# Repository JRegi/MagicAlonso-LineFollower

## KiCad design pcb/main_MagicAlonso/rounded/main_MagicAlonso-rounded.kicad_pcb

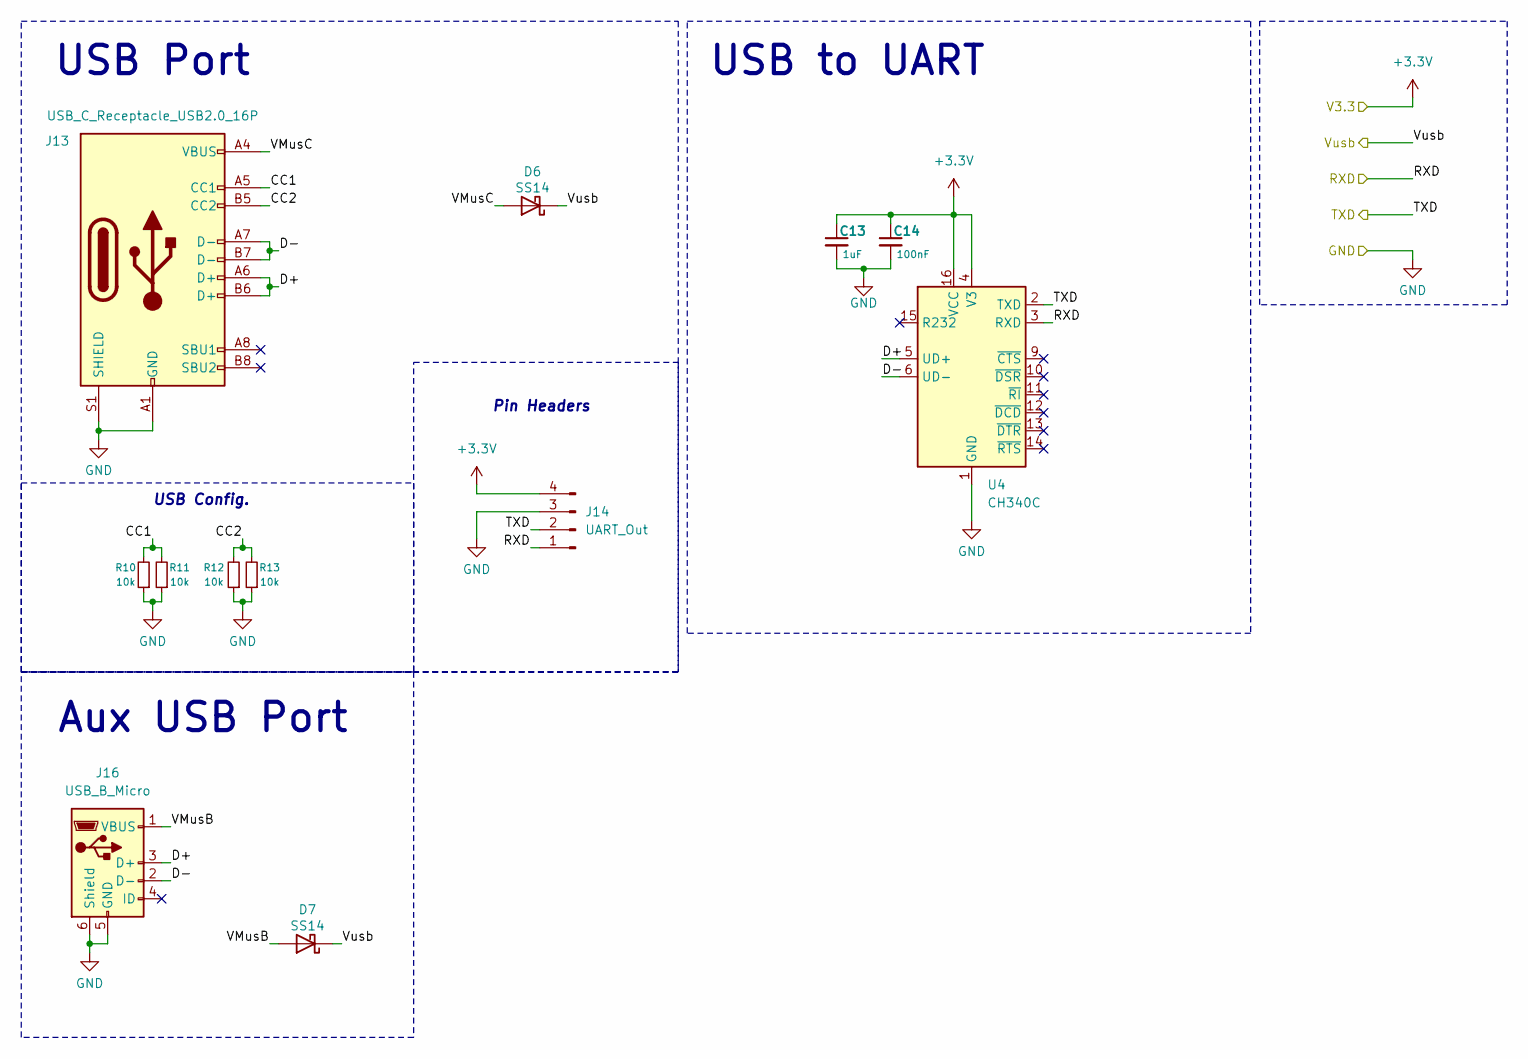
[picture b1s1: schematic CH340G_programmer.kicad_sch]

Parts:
C13: 1uF; C_0805_2012Metric
C14: 100nF; C_0603_1608Metric
D6, D7: SS14; D_SMA
J13: USB_C_Receptacle_USB2.0_16P; USB_C_Receptacle_GCT_USB4110
J14: UART_Out; JST_XH_S4B-XH-A_1x04_P2.50mm_Horizontal
J16: USB_B_Micro; USB_Micro-B_Amphenol_10104110_Horizontal
R10, R11, R12, R13: 10k; R_0603_1608Metric
U4: CH340C; SOIC-16_3.9x9.9mm_P1.27mm

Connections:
+3.3V: C13.1, C14.1, J14.4, U4.4 (V3), U4.16 (VCC); also elsewhere on the board
/CH340C/CC1: J13.A5 (CC1), R10.2, R11.2
/CH340C/CC2: J13.B5 (CC2), R12.2, R13.2
/CH340C/D+: J13.A6 (D+), J13.B6 (D+), J16.3 (D+), U4.5 (UD+)
/CH340C/D-: J13.A7 (D-), J13.B7 (D-), J16.2 (D-), U4.6 (UD-)
/CH340C/VMusB: D7.2 (A), J16.1 (VBUS)
/CH340C/VMusC: D6.2 (A), J13.A4 (VBUS), J13.A9 (VBUS), J13.B4 (VBUS), J13.B9 (VBUS)
/RX: J14.1, U4.3 (RXD); also elsewhere on the board
/TX: J14.2, U4.2 (TXD); also elsewhere on the board
/Vb: D6.1 (K), D7.1 (K); also elsewhere on the board
GND: C13.2, C14.2, J13.A1 (GND), J13.A12 (GND), J13.B1 (GND), J13.B12 (GND), J13.S1 (SHIELD), J14.3, J16.5 (GND), J16.6 (Shield), R10.1, R11.1, R12.1, R13.1, U4.1 (GND); also elsewhere on the board

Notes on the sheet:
USB to UART
Pin Headers
USB Config.
USB Port
Aux USB Port

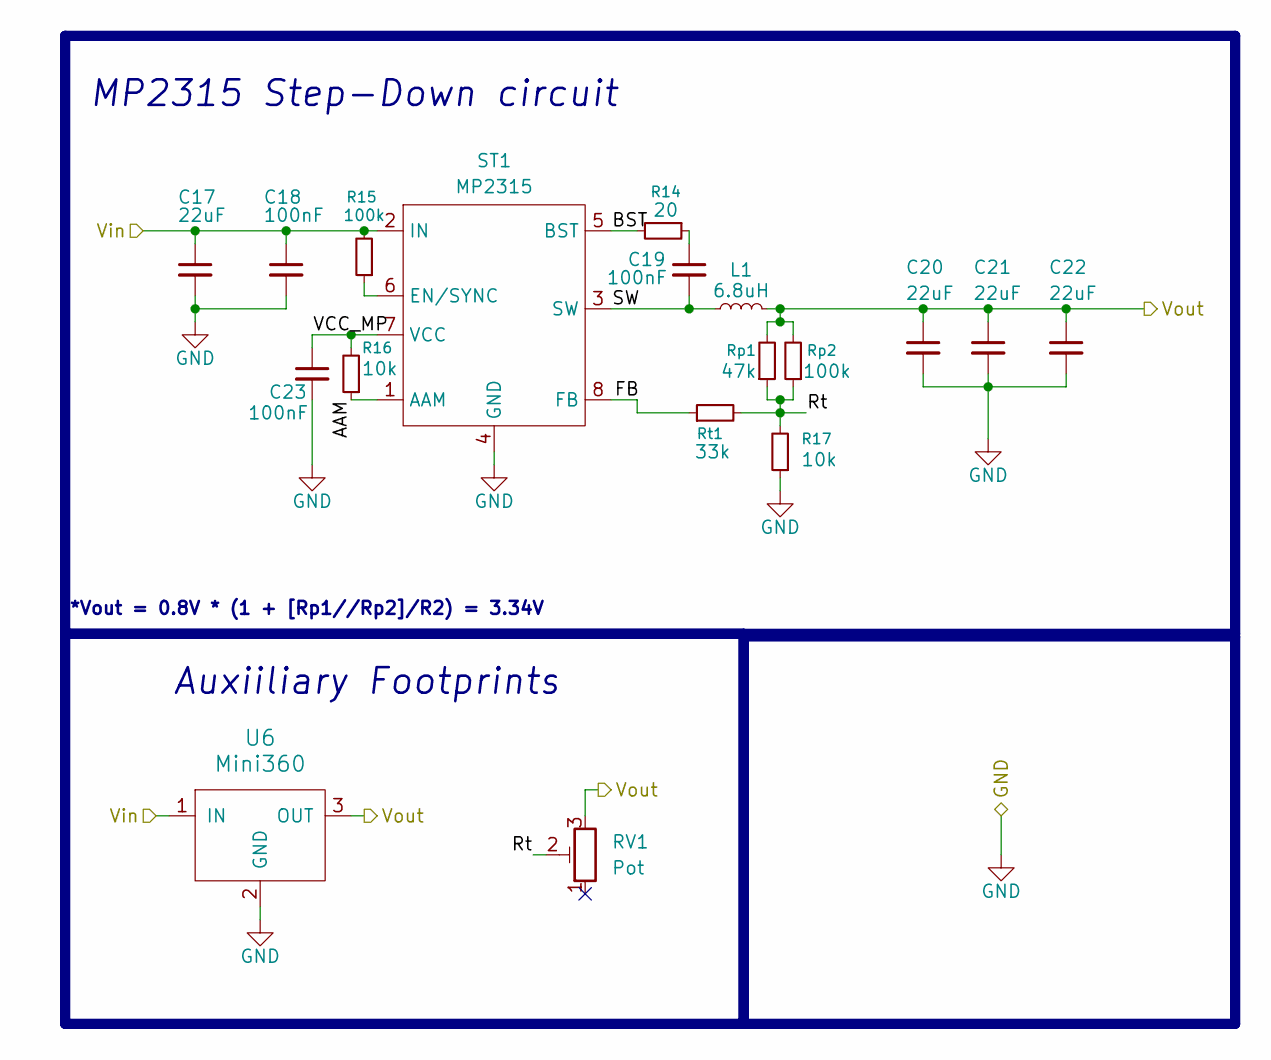
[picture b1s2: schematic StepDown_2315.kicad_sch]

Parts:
C17, C20, C21, C22: 22uF; C_0805_2012Metric
C18, C19, C23: 100nF; C_0603_1608Metric
L1: 6.8uH; L_TDK_SLF6025
R14: 20; R_0805_2012Metric
R15: 100k; R_0603_1608Metric
R16: 10k; R_0603_1608Metric
R17: 10k; R_0805_2012Metric
RV1: Pot; Potentiometer_Vishay_TS53YJ_Vertical
Rp1: 47k; R_0805_2012Metric
Rp2: 100k; R_0805_2012Metric
Rt1: 33k; R_0603_1608Metric
ST1: MP2315; TSOT-23-8
U6: Mini360; Mini360_step-down

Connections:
+3.3V: C20.1, C21.1, C22.1, L1.2, RV1.3, Rp1.2, Rp2.2, U6.3 (OUT); also elsewhere on the board
/StepDown_2315/AAM: R16.1, ST1.1 (AAM)
/StepDown_2315/BST: R14.2, ST1.5 (BST)
/StepDown_2315/FB: Rt1.1, ST1.8 (FB)
/StepDown_2315/Rt: R17.2, RV1.2, Rp1.1, Rp2.1, Rt1.2
/StepDown_2315/SW: C19.2, L1.1, ST1.3 (SW)
/StepDown_2315/VCC_SW: C23.1, R16.2, ST1.7 (VCC)
/Vb: C17.1, C18.1, R15.2, ST1.2 (IN), U6.1 (IN); also elsewhere on the board
GND: C17.2, C18.2, C20.2, C21.2, C22.2, C23.2, R17.1, ST1.4 (GND), U6.2 (GND); also elsewhere on the board
unnamed: C19.1, R14.1
unnamed: R15.1, ST1.6 (EN/SYNC)

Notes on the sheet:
*Vout = 0.8V * (1 + [Rp1//Rp2]/R2) = 3.34V
Auxiiliary Footprints
MP2315 Step-Down circuit

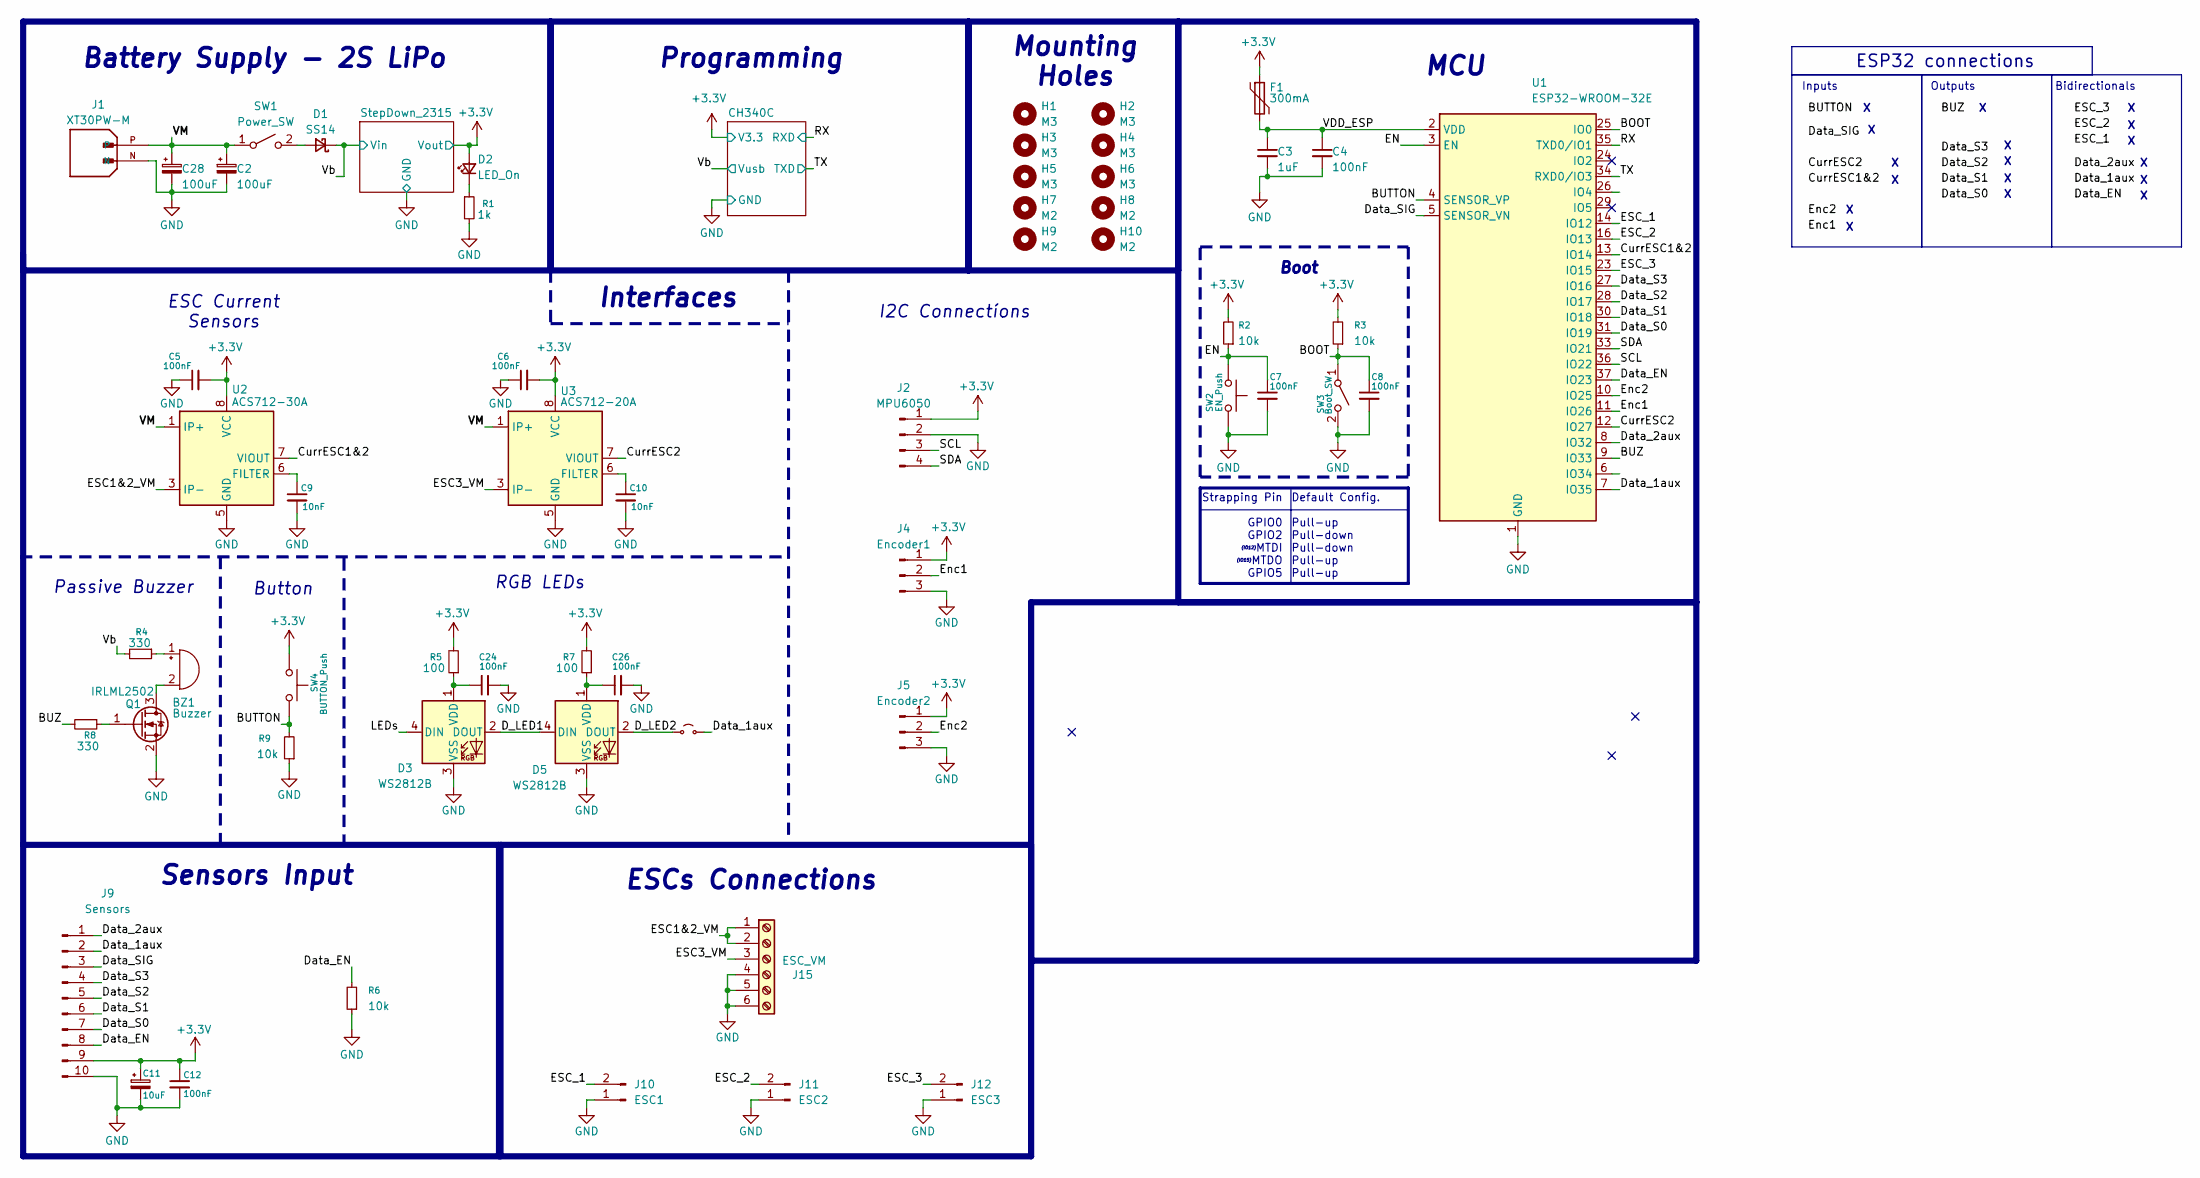
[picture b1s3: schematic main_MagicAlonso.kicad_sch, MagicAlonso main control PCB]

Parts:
BZ1: Buzzer; Buzzer_12x9.5RM7.6
C2, C28: 100uF; CP_Elec_6.3x5.4
C3: 1uF; C_0805_2012Metric
C4, C7, C12, C24, C26: 100nF; C_0805_2012Metric
C5, C6, C8: 100nF; C_0603_1608Metric
C9, C10: 10nF; C_0805_2012Metric
C11: 10uF; C_0805_2012Metric
D1: SS14; D_SMA
D2: LED_On; LED_0805_2012Metric
D3, D5: WS2812B; LED_WS2812B_PLCC4_5.0x5.0mm_P3.2mm
F1: 300mA; Fuse_1812_4532Metric_Pad1.30x3.40mm_HandSolder
H1, H2, H3, H4, H5, H6: M3; MountingHole_3mm
H7, H8, H9, H10: M2; MountingHole_2.2mm_M2
J1: XT30PW-M; AMASS_XT30PW-M; PARTREV 1.2
J2: MPU6050; MPU6050_Module
J4: Encoder1; JST_XH_B3B-XH-A_1x03_P2.50mm_Vertical
J5: Encoder2; JST_XH_B3B-XH-A_1x03_P2.50mm_Vertical
J9: Sensors; JST_XH_S10B-XH-A_1x10_P2.50mm_Horizontal
J10: ESC1; JST_XH_S2B-XH-A_1x02_P2.50mm_Horizontal
J11: ESC2; JST_XH_S2B-XH-A_1x02_P2.50mm_Horizontal
J12: ESC3; JST_XH_S2B-XH-A_1x02_P2.50mm_Horizontal
J15: ESC_VM; TerminalBlock_Phoenix_PT-1,5-6-3.5-H_1x06_P3.50mm_Horizontal
JP1: Jumper_2_Small_Open; R_1206_3216Metric
Q1: IRLML2502; SOT-23
R1: 1k; R_0603_1608Metric
R2, R3: 10k; R_0603_1608Metric
R4: 330; R_1206_3216Metric
R5, R7: 100; R_0805_2012Metric
R6, R9: 10k; R_0805_2012Metric
R8: 330; R_0805_2012Metric
SW1: Power_SW; SW_Slide-03_P2.54_L9_W4_H7
SW2: EN_Push; SW_SPST_CK_RS282G05A3
SW3: Boot_SW; SW_Slide-03_P2.54_L9_W4_H7
SW4: BUTTON_Push; SW_SPST_CK_RS282G05A3
U1: ESP32-WROOM-32E
U2: ACS712-30A; SOIC-8_3.9x4.9mm_P1.27mm
U3: ACS712-20A; SOIC-8_3.9x4.9mm_P1.27mm

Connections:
+3.3V: C5.2, C6.2, C11.1, C12.1, D2.2 (A), F1.1, J2.1, J4.1, J5.1, J9.9, R2.2, R3.2, R5.2, R7.2, SW4.1, U2.8 (VCC), U3.8 (VCC); also elsewhere on the board
/BOOT: C8.1, R3.1, SW3.1 (A), U1.25 (IO0)
/BUTTON: R9.2, SW4.2, U1.4 (SENSOR_VP)
/BUZ: R8.2, U1.9 (IO33)
/CurrESC1&2: U1.13 (IO14), U2.7 (VIOUT)
/CurrESC2: U1.12 (IO27), U3.7 (VIOUT)
/D_LED: D3.2 (DOUT), D5.4 (DIN)
/Data_1aux: J9.2, JP1.2 (B), U1.7 (IO35)
/Data_2aux: J9.1, U1.8 (IO32)
/Data_EN: J9.8, R6.2, U1.37 (IO23)
/Data_S0: J9.7, U1.31 (IO19)
/Data_S1: J9.6, U1.30 (IO18)
/Data_S2: J9.5, U1.28 (IO17)
/Data_S3: J9.4, U1.27 (IO16)
/Data_SIG: J9.3, U1.5 (SENSOR_VN)
/EN: C7.1, R2.1, SW2.1, U1.3 (EN)
/ESC1&2_VM: J15.1, J15.2, U2.3 (IP-), U2.4 (IP-)
/ESC3_VM: J15.3, U3.3 (IP-), U3.4 (IP-)
/ESC_1: J10.2, U1.14 (IO12)
/ESC_2: J11.2, U1.16 (IO13)
/ESC_3: J12.2, U1.23 (IO15)
/Enc1: J4.2, U1.11 (IO26)
/Enc2: J5.2, U1.10 (IO25)
/LEDs: D3.4 (DIN)
/RX: U1.35 (TXD0/IO1); also elsewhere on the board
/SCL: J2.3, U1.36 (IO22)
/SDA: J2.4, U1.33 (IO21)
/TX: U1.34 (RXD0/IO3); also elsewhere on the board
/VDD_ESP: C3.1, C4.1, F1.2, U1.2 (VDD)
/VM: C2.1, C28.1, J1.P, SW1.1 (A), U2.1 (IP+), U2.2 (IP+), U3.1 (IP+), U3.2 (IP+)
/Vb: D1.1 (K), R4.2; also elsewhere on the board
GND: C2.2, C3.2, C4.2, C5.1, C6.1, C7.2, C8.2, C9.2, C10.2, C11.2, C12.2, C24.2, C26.2, C28.2, D3.3 (VSS), D5.3 (VSS), J1.N, J2.2, J4.3, J5.3, J9.10, J10.1, J11.1, J12.1, J15.4, J15.5, J15.6, Q1.2 (S), R1.2, R6.1, R9.1, SW2.2, SW3.2 (B), U1.1 (GND), U1.15 (GND), U1.38 (GND), U1.39 (GND), U2.5 (GND), U3.5 (GND); also elsewhere on the board
unnamed: BZ1.1 (+), R4.1
unnamed: BZ1.2 (-), Q1.3 (D)
unnamed: D1.2 (A), SW1.2 (B)
unnamed: D2.1 (K), R1.1
unnamed: C24.1, D3.1 (VDD), R5.1
unnamed: C26.1, D5.1 (VDD), R7.1
unnamed: D5.2 (DOUT), JP1.1 (A)
unnamed: Q1.1 (G), R8.1
unnamed: C9.1, U2.6 (FILTER)
unnamed: C10.1, U3.6 (FILTER)

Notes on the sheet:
ESC Current Sensors
Strapping Pin GPIO0 GPIO2 MTDI MTDO GPIO5
Inputs
(IO12)
Passive Buzzer
(IO15)
I2C Connectíons
Mounting Holes
ESP32 connections
Battery Supply - 2S LiPo
Sensors Input
MCU
ESCs Connections
Boot
RGB LEDs
Outputs
Button
Interfaces
Bidirectionals
Default Config. Pull-up Pull-down Pull-down Pull-up Pull-up
Programming

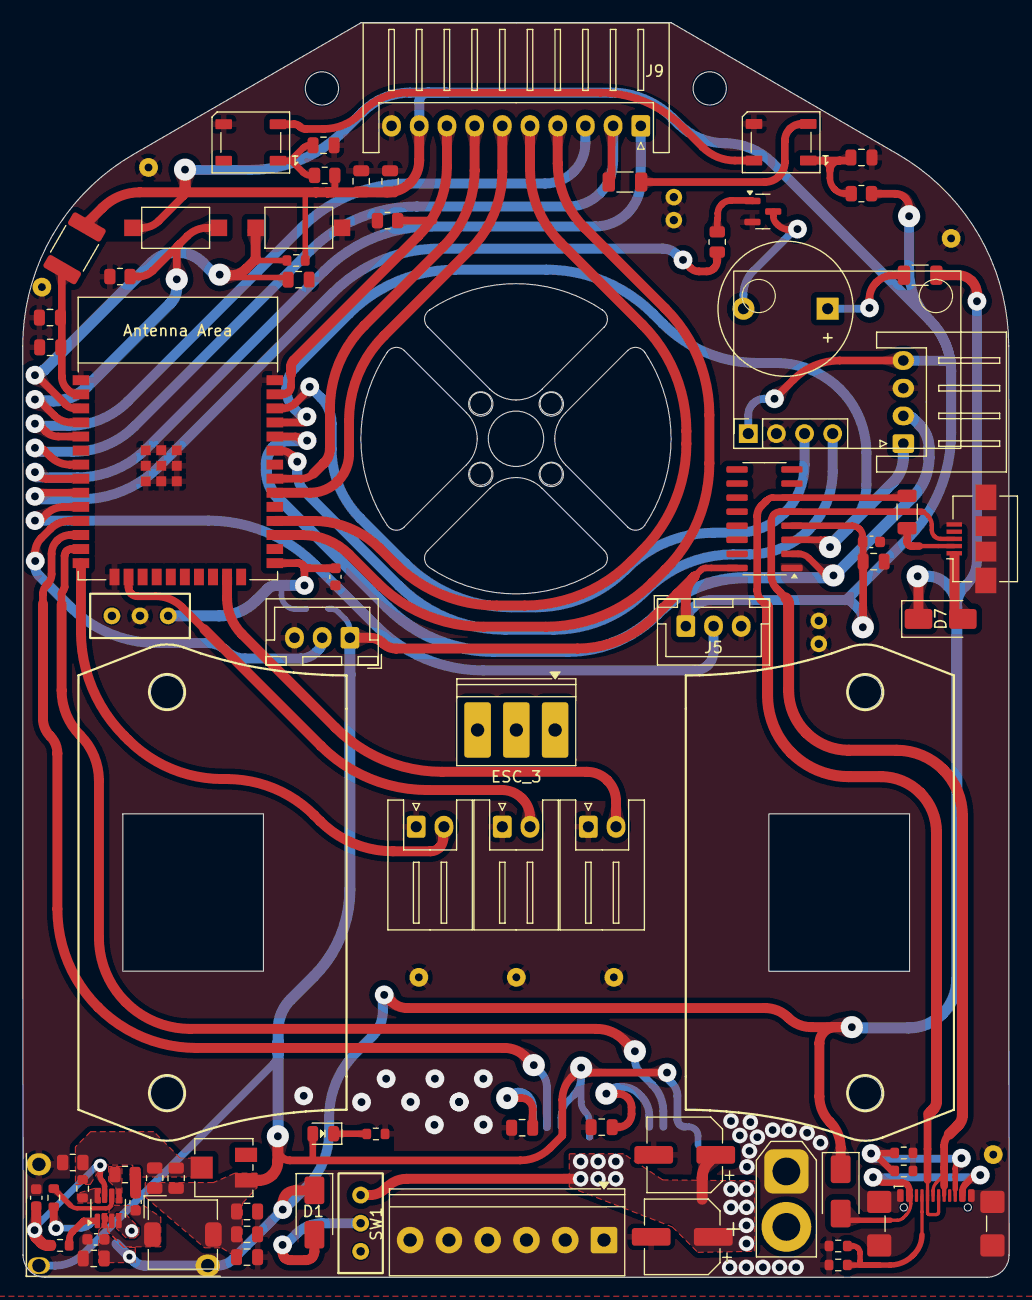
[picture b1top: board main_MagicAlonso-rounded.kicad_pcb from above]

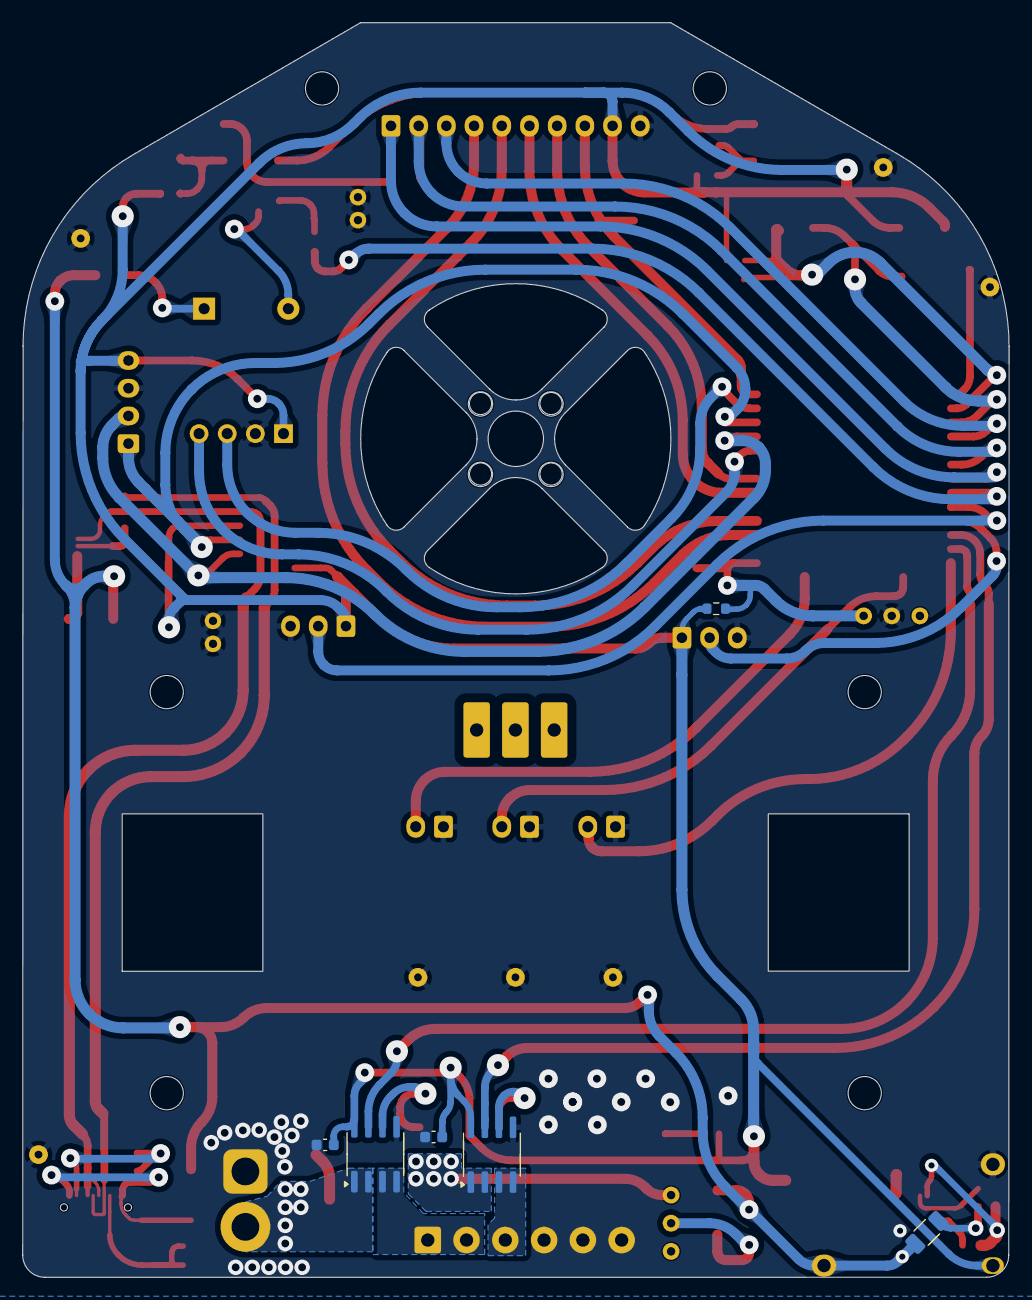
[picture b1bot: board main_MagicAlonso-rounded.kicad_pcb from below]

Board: 2 copper layers, 89.0 x 113.2 mm, 87 parts (5 on the bottom side), 54 nets.

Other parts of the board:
ESC_3: TerminalBlock_Phoenix_PT-1,5-3-3.5-H_1x03_P3.50mm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; TerminalBlock_Phoenix_PT-1,5-3-3.5-H_1x03_P3.50mm_Horizontal
